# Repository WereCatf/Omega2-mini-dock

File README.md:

# ERRATA
I've made a mistake with the ESD-protection, the USB-port doesn't work right
with the capacitor and resistor in place. Removing them allows for the USB-port
to work, it just will be less-protected. I'll fix it later.

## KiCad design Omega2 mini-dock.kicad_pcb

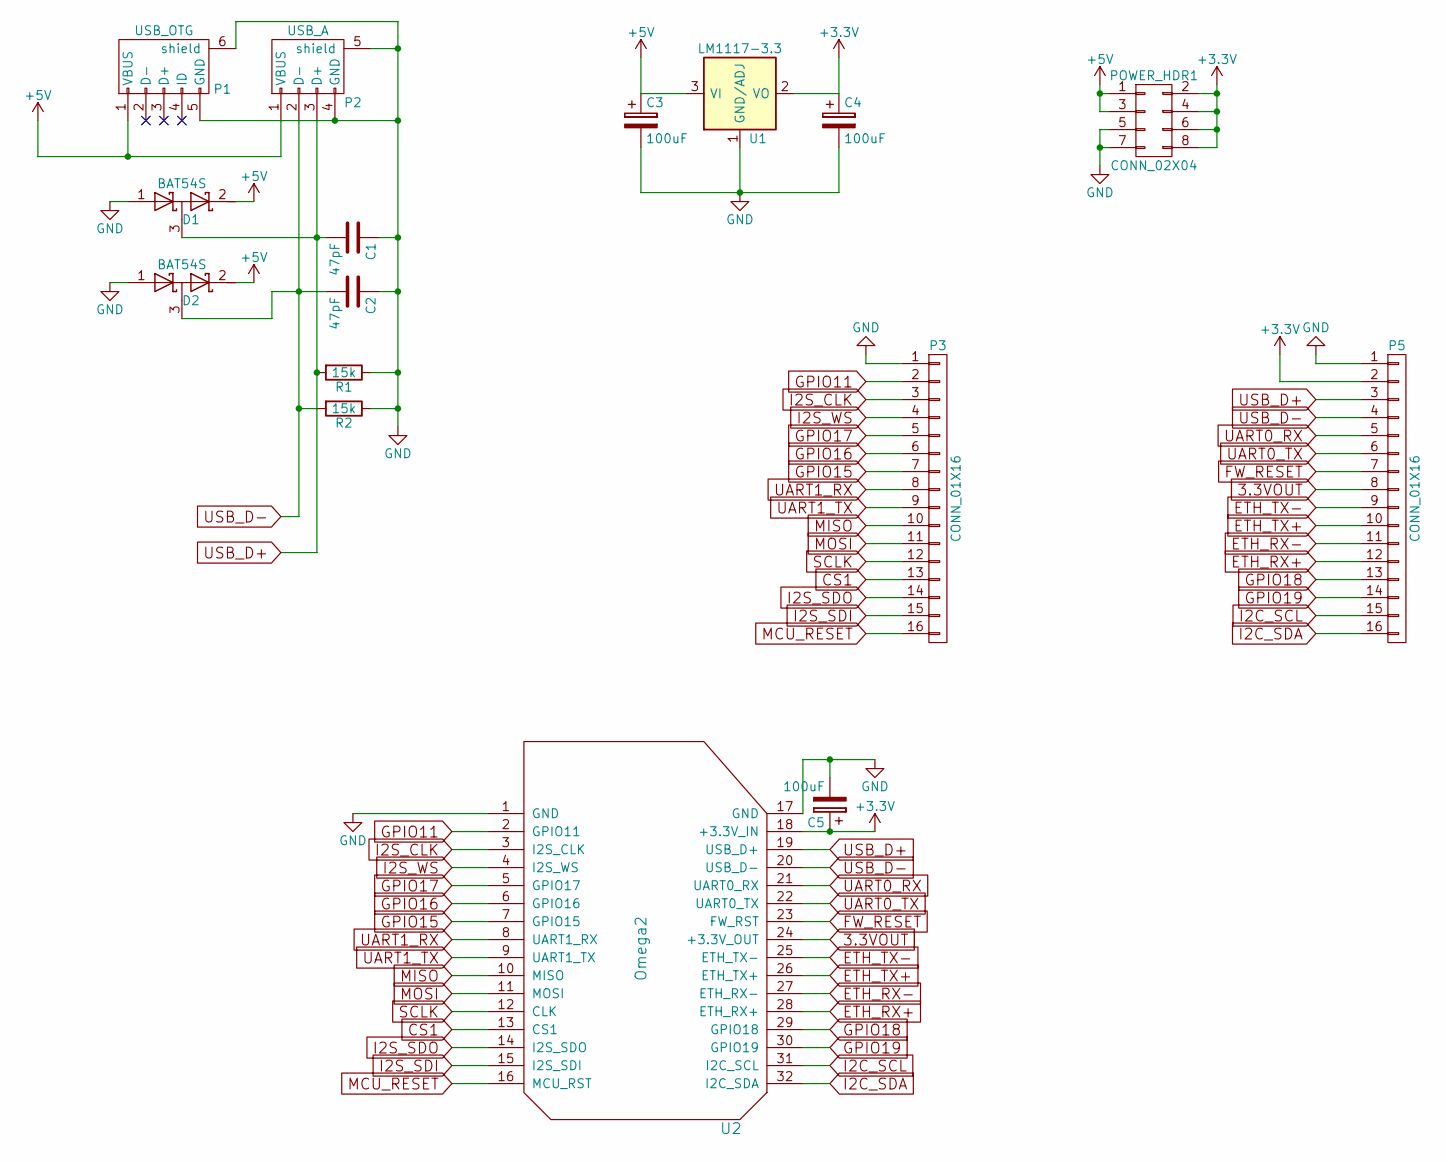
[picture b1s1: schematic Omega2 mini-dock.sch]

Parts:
C1, C2: 47pF; C_0805_HandSoldering
C3, C4, C5: 100uF; CP_Tantalum_Case-A_EIA-3216-18_Hand
D1, D2: BAT54S; SOT-23
P1: USB_OTG; USB_Micro-B
P2: USB_A
P3, P5: CONN_01X16; Pin_Header_Straight_1x16_Pitch2.54mm
POWER_HDR1: CONN_02X04; Pin_Header_Straight_2x04_Pitch2.54mm
R1, R2: 15k; R_0805_HandSoldering
U1: LM1117-3.3; SOT-223
U2: Omega2

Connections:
3.3VOUT: P5.8, U2.24 (+3.3V_OUT)
+3V3: C4.1, C5.1, P5.2, POWER_HDR1.2, POWER_HDR1.4, POWER_HDR1.6, POWER_HDR1.8, U1.2 (VO), U1.4 (VO), U2.18 (+3.3V_IN); also elsewhere on the board
+5V: C3.1, D1.2 (K), D2.2 (K), P1.1 (VBUS), P2.1 (VBUS), POWER_HDR1.1, POWER_HDR1.3, U1.3 (VI); also elsewhere on the board
CS1: P3.13, U2.13 (CS1)
ETH_RX+: P5.12, U2.28 (ETH_RX+)
ETH_RX-: P5.11, U2.27 (ETH_RX-)
ETH_TX+: P5.10, U2.26 (ETH_TX+)
ETH_TX-: P5.9, U2.25 (ETH_TX-)
FW_RESET: P5.7, U2.23 (FW_RST)
GND: C1.1, C2.1, C3.2, C4.2, C5.2, D1.1 (A), D2.1 (A), P1.5 (GND), P1.6 (shield), P2.4 (GND), P2.5 (shield), P3.1, P5.1, POWER_HDR1.5, POWER_HDR1.7, R1.1, R2.1, U1.1 (GND/ADJ), U2.1 (GND), U2.17 (GND); also elsewhere on the board
GPIO11: P3.2, U2.2 (GPIO11)
GPIO15: P3.7, U2.7 (GPIO15)
GPIO16: P3.6, U2.6 (GPIO16)
GPIO17: P3.5, U2.5 (GPIO17)
GPIO18: P5.13, U2.29 (GPIO18)
GPIO19: P5.14, U2.30 (GPIO19)
I2C_SCL: P5.15, U2.31 (I2C_SCL)
I2C_SDA: P5.16, U2.32 (I2C_SDA)
I2S_CLK: P3.3, U2.3 (I2S_CLK)
I2S_SDI: P3.15, U2.15 (I2S_SDI)
I2S_SDO: P3.14, U2.14 (I2S_SDO)
I2S_WS: P3.4, U2.4 (I2S_WS)
MCU_RESET: P3.16, U2.16 (MCU_RST)
MISO: P3.10, U2.10 (MISO)
MOSI: P3.11, U2.11 (MOSI)
SCLK: P3.12, U2.12 (CLK)
UART0_RX: P5.5, U2.21 (UART0_RX)
UART0_TX: P5.6, U2.22 (UART0_TX)
UART1_RX: P3.8, U2.8 (UART1_RX)
UART1_TX: P3.9, U2.9 (UART1_TX)
USB_D+: C1.2, D1.3 (common), P2.3 (D+), P5.3, R1.2, U2.19 (USB_D+)
USB_D-: C2.2, D2.3 (common), P2.2 (D-), P5.4, R2.2, U2.20 (USB_D-)

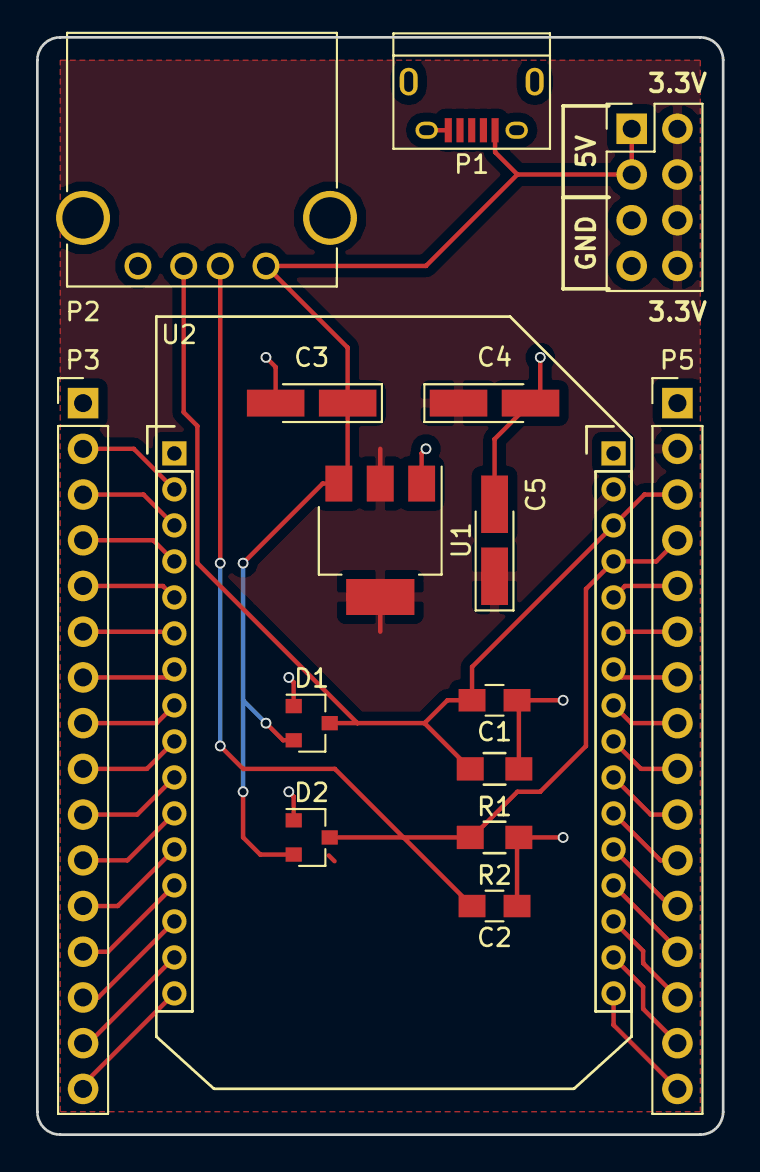
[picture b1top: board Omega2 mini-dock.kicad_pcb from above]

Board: 2 copper layers, 38.1 x 61.0 mm, 16 parts (0 on the bottom side), 32 nets.

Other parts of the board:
POWER: CONN_02X04; Pin_Header_Straight_2x04_Pitch2.54mm

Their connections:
+3V3: POWER.2, POWER.4, POWER.6, POWER.8; also elsewhere on the board
+5V: POWER.1, POWER.3; also elsewhere on the board
GND: POWER.5, POWER.7; also elsewhere on the board

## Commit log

2017-02-22 :space_invader: Added .gitattributes
2017-02-22 First release
    This is my take on a minimalistic dock for the Onion Omega2/2+
2017-02-22 Add .gitignore
2017-02-24 Some tuning on the visuals
2017-03-20 Add README.md

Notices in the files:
Omega2 mini-dock.kicad_pcb:
Public Domain
